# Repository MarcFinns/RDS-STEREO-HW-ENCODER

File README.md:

# RDS Stereo Encoder for FM radio 

A hardware RDS Stereo Encoder for FM radio comprised of:
- A signal processing board
- A digital board that provides a transparent communication bridge between PC RDS software and the DS encoder chips, while simultaneously providing real-time visual display of RDS data (PS/RT) and audio levels (VU meters) on a TFT display.

## System Overview

This project specifically describes the software implementation of the digital board. The schematic and PCB of the whole system are in the **HARDWARE** folder.

### Key Features

- **Dual-core ESP32 processing** for optimal performance
- **FreeRTOS task-based design** with priority optimization
- **Queue-based inter-task communication** for thread safety
- **Collision avoidance system** for seamless PC-MRDS1322 bridging
- **Real-time graphics** with ~60 FPS VU meter updates
- **Professional VU meters** with color-coded zones and peak detection

## Hardware Requirements

### Main Components
- **ESP32 DevKit** (dual-core processing)
- **MRDS1322 RDS encoder chip**
- **NV3007 428x142 TFT display**
- **Dual-channel audio input** for VU meters

### Hardware Design Files

The **`hardware/`** folder contains the complete PCB design for this project, including schematics and PCB layout. This hardware has been **built and fully tested** in real-world conditions.

### MRDS1322 RDS Encoder

The **MRDS1322** RDS encoder chip is from [Pira.cz](http://pira.cz). Datasheet available in the `hardware/` folder. Use the **TinyRDS** Windows program (also from Pira.cz) to send RDS data through this ESP32 bridge to the encoder.

## Pin Assignments

### TFT Display (NV3007) - SPI Interface
```
ESP32 Pin | Function    | NV3007 Pin
----------|-------------|-------------
GPIO19    | SCLK        | SCK
GPIO18    | MOSI        | SDA
GPIO16    | CS          | CS
GPIO17    | DC/RS       | DC
GPIO5     | RST         | RES
GPIO4     | Backlight   | LED
3.3V      | Power       | VCC
GND       | Ground      | GND
```

### Serial Communication
```
Interface | ESP32 Pin    | Baud Rate | Purpose
----------|------------- |-----------|------------------
Serial    | USB          | 19200     | PC Communication
Serial1   | GPIO21 (RX)  | 19200     | MRDS1322 RDS Chip
          | GPIO22 (TX)  |           |
```

### VU Meters - Audio Input (ADC)
```
Channel | ESP32 Pin | ADC Channel | Purpose
--------|-----------|-------------|----------------
Left    | GPIO39    | ADC1_CH3    | Left audio input
Right   | GPIO36    | ADC1_CH0    | Right audio input
```

### Complete Pin Reference Table
All pin assignments are centralized in `SharedTypes.h` for easy modification:

```
┌──────────────┬─────────────────────┬──────────────────────────┐
│ ESP32 GPIO   │ Function            │ Connected To             │
├──────────────┼─────────────────────┼──────────────────────────┤
│ GPIO21       │ SERIAL1_RX          │ MRDS1322 TX              │
│ GPIO22       │ SERIAL1_TX          │ MRDS1322 RX              │
│ GPIO16       │ TFT_CS              │ NV3007 Chip Select       │
│ GPIO5        │ TFT_RST             │ NV3007 Reset             │
│ GPIO17       │ TFT_DC              │ NV3007 Data/Command      │
│ GPIO18       │ TFT_MOSI            │ NV3007 SPI Data          │
│ GPIO19       │ TFT_SCLK            │ NV3007 SPI Clock         │
│ GPIO4        │ TFT_BL              │ NV3007 Backlight         │
│ GPIO39 (A3)  │ PIN_L (ADC1_CH3)    │ Left Audio Input         │
│ GPIO36 (A0)  │ PIN_R (ADC1_CH0)    │ Right Audio Input        │
│ USB (N/A)    │ Serial (PC Comm)    │ PC USB Connection        │
└──────────────┴─────────────────────┴──────────────────────────┘
```

**Note**: All pin defines are located in `SharedTypes.h` lines 136-151. To change pin assignments for PCB design, simply modify the `#define` values in that single location.

## System Architecture

### Communication Flow
```
PC Software → Serial USB → ESP32 Core 0 → Serial1 → MRDS1322
                ↓              ↓
         Response Routing  PS/RT Monitoring
                ↓              ↓
            PC Software    Core 1 → TFT Display
                               ↓
                          VU Meters (GPIO36/39)
```

### Task Architecture
- **CommunicationManager** (Core 0, Priority 1): PC-MRDS1322 bridging
- **DisplayManager** (Core 1, Priority 2): TFT graphics + VU meters
- **Queue-based data exchange** for thread-safe operation

## Display Layout

### TFT Display (428x142, Landscape)
```
┌─────────────────────────────────┐ ← Y=10
│         STATION ID              │   Station area (30px tall)
│      (Cyan, Size 3)             │   Auto-centered, space-trimmed
├─────────────────────────────────┤ ← Y=38
│   Scrolling Radio Text...       │   Text area (25px tall)
│     (White, Size 2)             │   Sliding window scrolling
├─────────────────────────────────┤ ← Y=75
│ L ████████████████████████████  │   VU Left (18px tall)
│   |   |  |  ||  |     dB Scale  │   Professional scale with
│  -20 -10 -3  0 +3   (colored)   │   color-coded bold labels
│   |   |  |  ||  |               │
│ R ████████████████████████████  │   VU Right (18px tall)
└─────────────────────────────────┘ ← Y=142
```

### VU Meter Features
- **Color-coded bars**: Green (safe) → Yellow (loud) → Orange (hot) → Red (peak)
- **Professional dB scale**: Centered between bars with color-coded bold labels
  - **-20/-10 dB**: Green (safe levels)
  - **-3 dB**: Yellow (caution level)
  - **0 dB**: White (reference level)
  - **+3 dB**: Red (peak/overload warning)
- **Peak markers**: White bars showing recent maximum levels (1-second hold)
- **Smooth ballistics**: Fast attack, slow release for natural VU behavior

## MRDS1322 Protocol

### Memory Map
- **PS (Program Service)**: Address 0xC8, Length 8 bytes
- **RT (Radio Text)**: Address 0x20, Length 64 bytes

### Protocol Frame Structure
```
Read Command:  FE D0 [ADDR] [LEN] FF
Response:      FE [DATA...] FF

Byte Stuffing Rules:
- Data byte 0xFD → FD 00
- Data byte 0xFE → FD 01
- Data byte 0xFF → FD 02
```

## Configuration

### VU Meter Parameters
```cpp
#define SAMPLE_WINDOW 2       // Samples per level calculation
#define ATTACK_STEP 3         // Fast attack (pixels/step)
#define RELEASE_STEP 4        // Slow release (pixels/step)
#define DECAY_INTERVAL_MS 20  // Decay timing (20ms)
#define PEAK_HOLD_MS 1000     // Peak hold time (1 second)
```

### Text Scrolling
```cpp
#define SCROLL_DELAY_MS 50    // Base scroll timing (multiplied by 3 = 150ms actual)
#define SCROLL_STEP_SIZE 2    // Pixels to advance per step (smooth motion)
```

### Display Features
- **Station ID**: Auto-centers after trimming trailing spaces
- **Radio Text**: Sliding window scrolling for long text, centered for short text
- **VU Scale**: Professional dB scale with bold, color-coded labels

## Performance Specifications

- **VU Meter Update Rate**: ~60 FPS (16ms loop time)
- **Text Scroll Speed**: Character-by-character at ~6.7 FPS (150ms per step)
- **MRDS1322 Polling**: Every 2 seconds
- **Peak Marker Hold**: 1 second
- **Audio Sampling**: 12-bit ADC (0-4095 range)
- **Display Updates**: Change detection prevents unnecessary redraws

## Build Dependencies

### Required Libraries
```cpp
#include <Arduino.h>
#include <Arduino_GFX_Library.h>    // TFT display driver (NV3007)
#include "freertos/FreeRTOS.h"      // Real-time OS
#include "freertos/queue.h"         // Inter-task communication
#include "freertos/task.h"          // Task management
```

## File Structure

```
RDS_STEREO_ENCODER_CLEAN/
├── RDS_STEREO_ENCODER_CLEAN.ino  # Main Arduino sketch
├── CommunicationManager.h        # PC-MRDS1322 bridge header
├── CommunicationManager.cpp      # Communication implementation
├── DisplayManager.h              # Display management header
├── DisplayManager.cpp            # TFT/VU meter implementation
├── SharedTypes.h                 # Pin configuration & data structures
├── splashscreen.h                # Splash screen data header
├── splashscreen.cpp              # Splash screen bitmap data
└── README.md                     # This documentation
```

## Usage

1. **Hardware Setup**: Connect all components according to pin assignments
2. **Software Setup**: Install required libraries in Arduino IDE
3. **Configuration**: Adjust compile-time options in SharedTypes.h
4. **Upload**: Flash the code to ESP32 DevKit
5. **PC Software**: Connect RDS software to ESP32's Serial port at 19200 baud
6. **MRDS1322**: Connect RDS encoder chip to Serial1 at 19200 baud

## License

Created by Claude Code Assistant, 2024
Version 2.0

## Technical Notes

- The system uses ESP32's dual-core architecture for optimal performance
- Core 0 handles communication with lower priority for smooth graphics
- Core 1 handles display updates with higher priority for responsive VU meters
- Queue-based communication ensures thread-safe data exchange
- Change detection prevents unnecessary screen updates and reduces flicker
- Logarithmic audio scaling provides perceptual accuracy for VU meters

## Pin Configuration for PCB Design

All hardware pin assignments are centralized in **`SharedTypes.h`** (lines 136-151) under the section "ESP32 HARDWARE PIN CONFIGURATION". This design makes it easy to modify pins for custom PCB layouts:

1. **Serial Communication**: `SERIAL1_RX`, `SERIAL1_TX` (GPIO21/22)
2. **TFT Display**: `TFT_CS`, `TFT_RST`, `TFT_DC`, `TFT_MOSI`, `TFT_SCLK`, `TFT_BL` (GPIO16/5/17/18/19/4)
3. **VU Meter ADC**: `PIN_L`, `PIN_R` (GPIO39/36)

**To modify pins**: Simply edit the `#define` values in `SharedTypes.h`. The code automatically uses these definitions throughout - no need to search and replace in multiple files.

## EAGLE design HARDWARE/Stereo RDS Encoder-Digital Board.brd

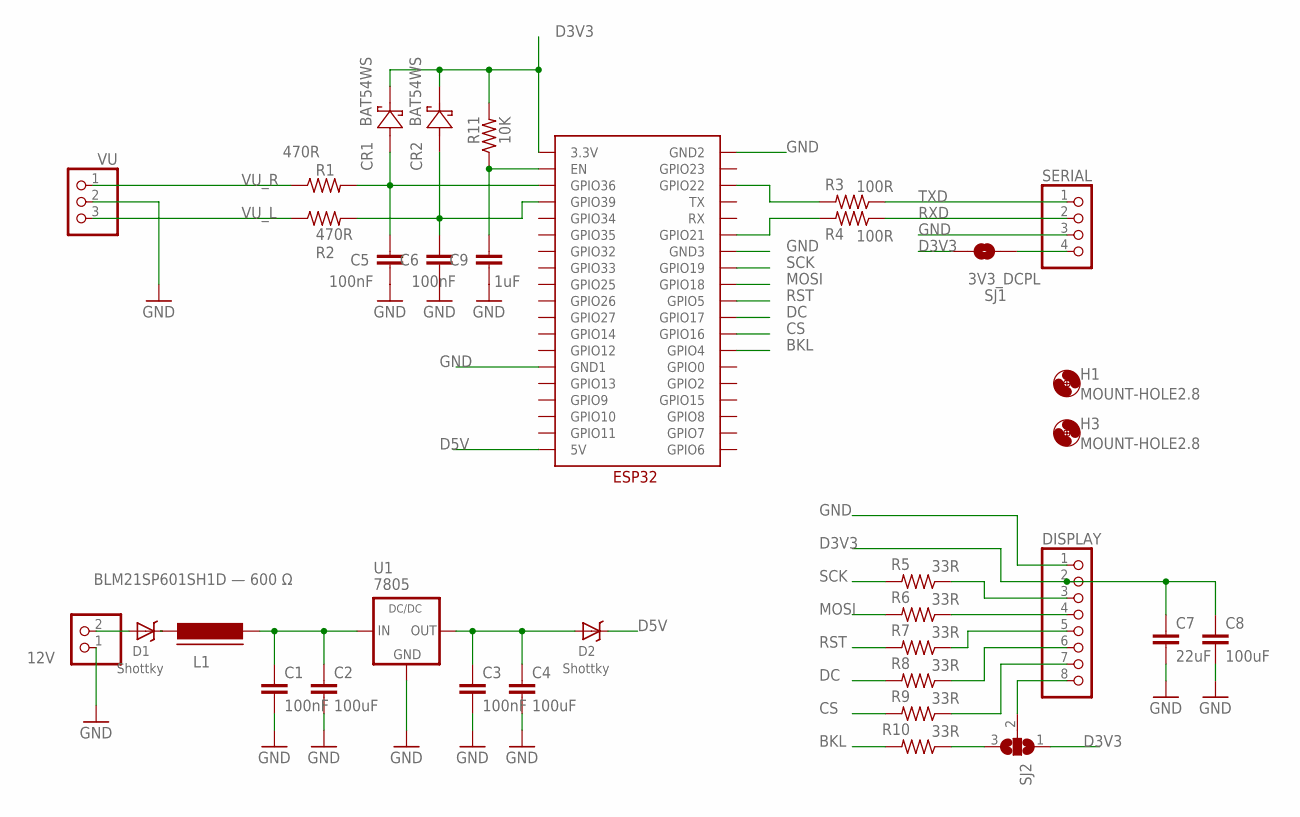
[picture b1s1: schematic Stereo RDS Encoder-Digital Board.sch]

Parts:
12V: PINHD-1X2; 1X02
C1, C3, C5, C6: 100nF; C0805
C2, C4, C8: 100uF; C0805
C7: 22uF; C0805
C9: 1uF; C0805
CR1, CR2: BAT54WS; SDO_SOD-323_VIS
D1, D2: Shottky; SMA-403D
DEV1: ESP32
DISPLAY: PINHD-1X8; 1X08
H1, H3: MOUNT-HOLE2.8; 2,8
L1: BLM21SP601SH1D — 600 Ω; FB805
R1, R2: 470R; M0805
R3, R4: 100R; M0805
R5, R6, R7, R8, R9, R10: 33R; M0805
R11: 10K; M0805
SERIAL: PINHD-1X4; 1X04
SJ1: 3V3_DCPL; SJ_2S-NO
SJ2: SJ2W; SJ_2
U1: 7805; R-78XX
VU: PINHD-1X3; 1X03

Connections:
BKL: DEV1.GPIO4, R10.2
CS: DEV1.GPIO16, R9.2
D3V3: C7.1, C8.1, CR1.1 (CATHODE), CR2.1 (CATHODE), DEV1.3.3V, DISPLAY.2, R11.2, SJ1.1, SJ2.1
D5V: D2.C, DEV1.5V
D5V1: C1.1, C2.1, L1.2, U1.1 (IN)
DC: DEV1.GPIO17, R8.2
GND: 12V.1, C1.2, C2.2, C3.2, C4.2, C5.2, C6.2, C7.2, C8.2, C9.2, DEV1.GND1, DEV1.GND2, DEV1.GND3, DISPLAY.1, SERIAL.3, U1.2 (GND), VU.2
MOSI: DEV1.GPIO18, R6.2
unnamed: R10.1, SJ2.3
unnamed: DEV1.GPIO21, R4.2
unnamed: DEV1.GPIO22, R3.2
unnamed: SERIAL.4, SJ1.2
unnamed: C9.1, DEV1.EN, R11.1
unnamed: D1.C, L1.1
unnamed: 12V.2, D1.A
unnamed: C5.1, CR1.2 (ANODE), DEV1.GPIO36, R1.2
unnamed: C6.1, CR2.2 (ANODE), DEV1.GPIO39, R2.2
unnamed: DISPLAY.3, R5.1
unnamed: DISPLAY.4, R6.1
unnamed: DISPLAY.5, R7.1
unnamed: DISPLAY.6, R8.1
unnamed: DISPLAY.7, R9.1
unnamed: DISPLAY.8, SJ2.2
unnamed: C3.1, C4.1, D2.A, U1.3 (OUT)
RST: DEV1.GPIO5, R7.2
RXD: R4.1, SERIAL.2
SCK: DEV1.GPIO19, R5.2
TXD: R3.1, SERIAL.1
VU_L: R2.1, VU.3
VU_R: R1.1, VU.1

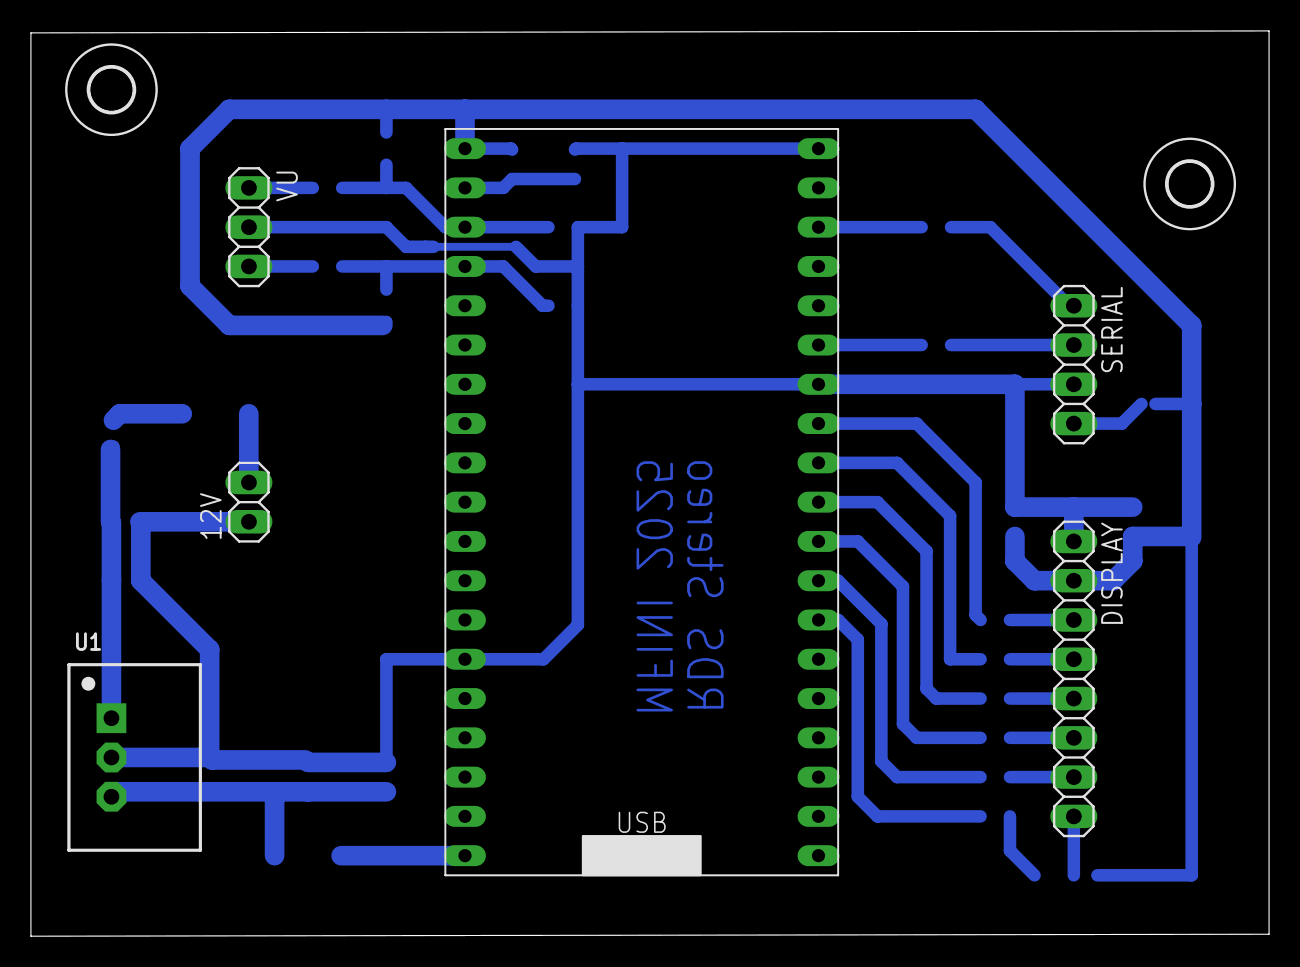
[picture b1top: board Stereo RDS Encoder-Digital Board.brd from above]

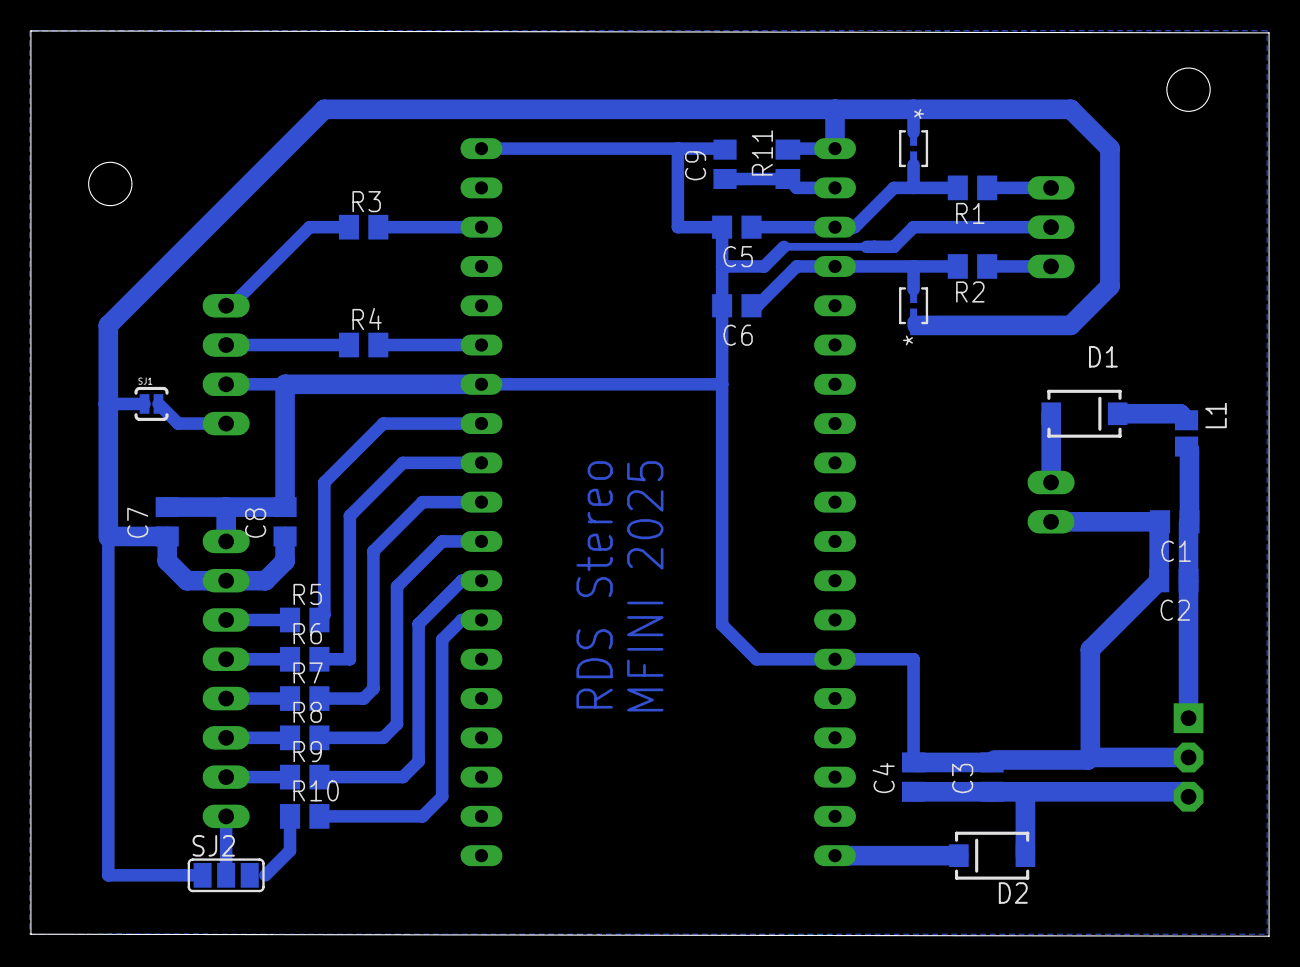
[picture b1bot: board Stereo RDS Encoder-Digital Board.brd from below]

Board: 2 copper layers, 80.1 x 58.5 mm, 35 parts (27 on the bottom side), 30 nets.

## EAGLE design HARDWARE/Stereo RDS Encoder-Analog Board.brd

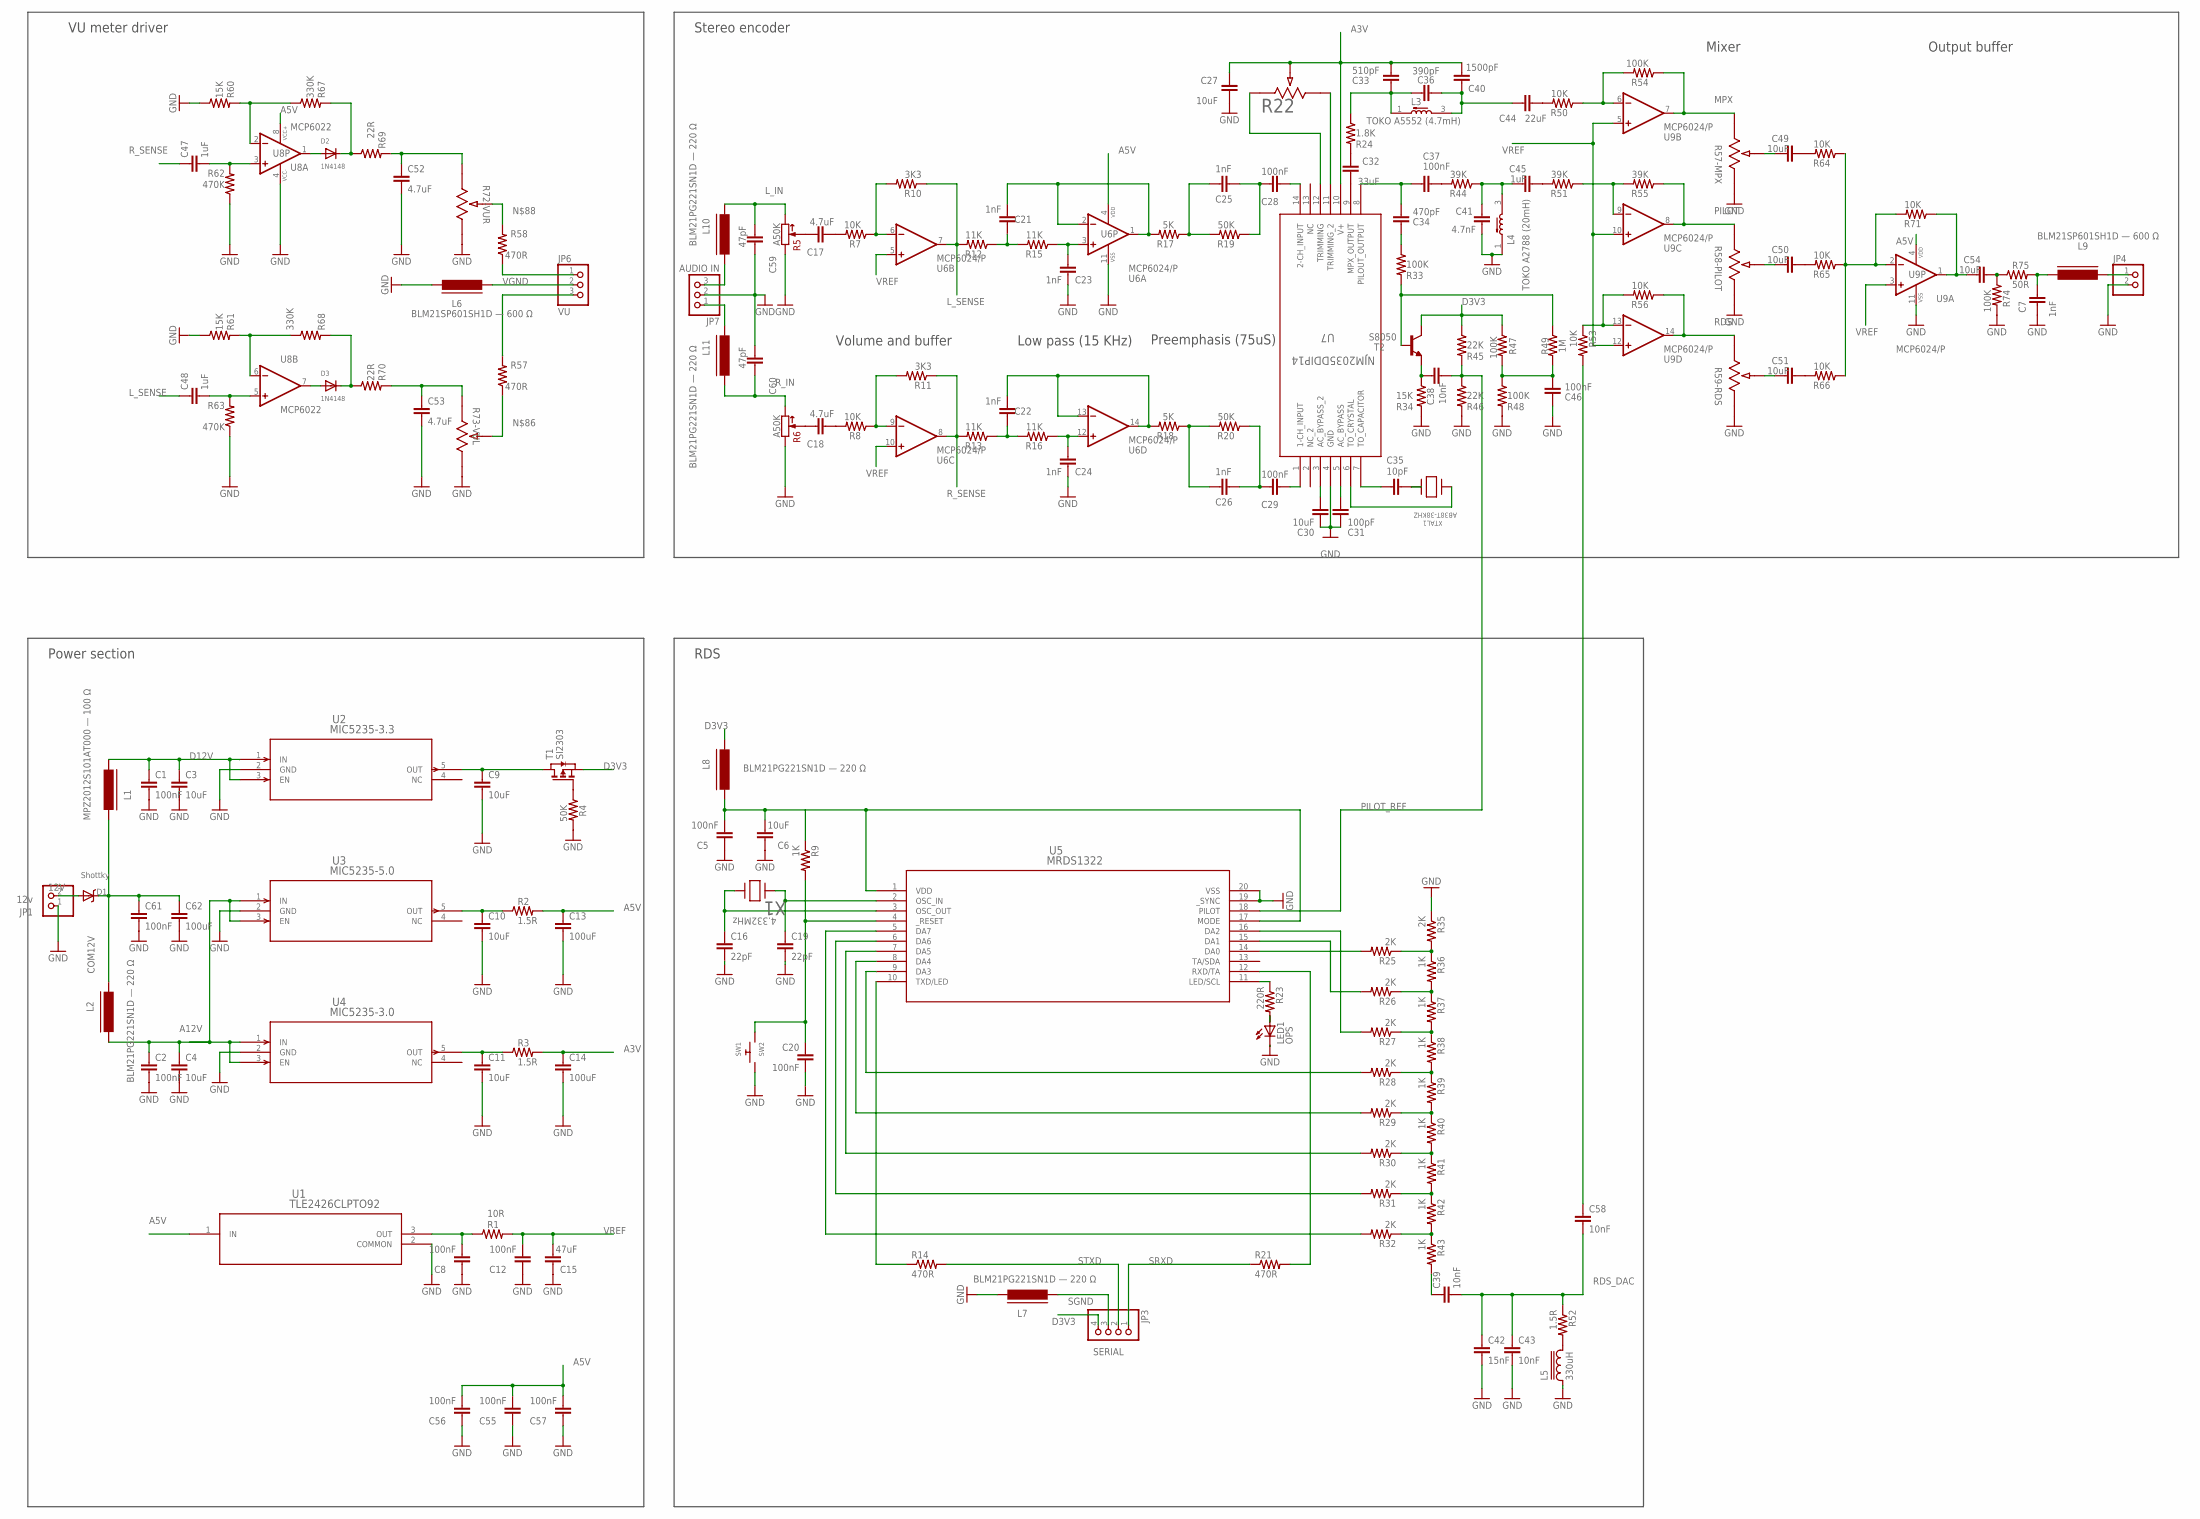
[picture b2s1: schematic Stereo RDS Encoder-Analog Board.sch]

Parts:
C1, C2, C5, C8, C12, C20, C28, C29, C37, C46, C55, C56, C57, C61: 100nF; C0805
C3, C4, C6, C9, C10, C11, C27, C30, C49, C50, C51, C54: 10uF; C0805
C7, C21, C22, C23, C24, C25, C26: 1nF; C0805
C13, C14, C62: 100uF; C0805
C15: 47uF; C0805
C16, C19: 22pF; C0805
C17, C18, C52, C53: 4.7uF; C0805
C31: 100pF; C0805
C32: 33uF; C0805
C33: 510pF; C0805
C34: 470pF; C0805
C35: 10pF; C0805
C36: 390pF; C0805
C38, C39, C43, C58: 10nF; C0805
C40: 1500pF; C0805
C41: 4.7nF; C0805
C42: 15nF; C0805
C44: 22uF; C0805
C45, C47, C48: 1uF; C0805
C59, C60: 47pF; C0805
D1: Shottky; SMA-403D
D2, D3: 1N4148; SOD-323F
JP1: 12v; 1X02
JP3: SERIAL; 1X04
JP4: PINHD-1X2; 1X02
JP6: VU; 1X03
JP7: AUDIO IN; 1X03
L1: MPZ2012S101AT000 — 100 Ω; FB805
L2, L7, L8, L10, L11: BLM21PG221SN1D — 220 Ω; FB805
L3: TOKO A5552 (4.7mH); 7KMM
L4: TOKO A2788 (20mH); 7KMM
L5: 330uH; 8RB
L6, L9: BLM21SP601SH1D — 600 Ω; FB805
LED1: OPS; CHIPLED_0805
R1: 10R; M0805
R2, R3, R52: 1.5R; M0805
R4, R19, R20: 50K; M0805
R5, R6: A50K; RV09-SINGLE
R7, R8, R50, R53, R56, R64, R65, R66, R71: 10K; M0805
R9, R36, R37, R38, R39, R40, R41, R42, R43: 1K; M0805
R10, R11: 3K3; M0805
R12, R13, R15, R16: 11K; M0805
R14, R21, R57, R58: 470R; M0805
R17, R18: 5K; M0805
R22, R57-MPX, R58-PILOT, R59-RDS, R72-VUR, R73-VUL: 50K; POT_3296W
R23: 220R; M0805
R24: 1.8K; M0805
R25, R26, R27, R28, R29, R30, R31, R32, R35: 2K; M0805
R33, R47, R48, R54, R74: 100K; M0805
R34, R60, R61: 15K; M0805
R44, R51, R55: 39K; M0805
R45, R46: 22K; M0805
R49: 1M; M0805
R62, R63: 470K; M0805
R67, R68: 330K; M0805
R69, R70: 22R; M0805
R75: 50R; M0805
SW1: SW2; BTN_CK_KSS
T1: SI2303; SOT-23
T2: S8050; SOT23
U1: TLE2426CLPTO92; TO92
U2: MIC5235-3.3; SOT-23-5_M5_MCH-M
U3: MIC5235-5.0; SOT-23-5_M5_MCH-M
U4: MIC5235-3.0; SOT-23-5_M5_MCH-M
U5: MRDS1322; PDIP20_300MC_MCH
U6, U9: MCP6024/P; DIL14
U7: NJM2035DDIP14; DIP14
U8: MCP6022; DIL08
X1: 4.332MHz; XTAL_HC-49/U-S_CFC
XTAL1: AB38T-38KHZ; XTAL_AB38T_ABR

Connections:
12V: D1.A, JP1.2
A3V: C14.1, C27.1, C33.1, C40.1, R3.2, R22.2, U7.10 (V+)
A5V: C13.1, C55.2, C56.2, C57.2, R2.2, U1.1 (IN), U6.4 (VDD), U8.8 (VCC+), U9.4 (VDD)
A12V: C2.1, C4.1, L2.2, U3.1 (IN), U3.3 (EN), U4.1 (IN), U4.3 (EN)
COM12V: C61.1, C62.1, D1.C, L1.1, L2.1
D3V3: JP3.4, L8.1, R45.1, R47.1, T1.2 (S), T2.3 (C)
D12V: C1.1, C3.1, L1.2, U2.1 (IN), U2.3 (EN)
GND: C1.2, C2.2, C3.2, C4.2, C5.1, C6.1, C7.1, C8.1, C9.2, C10.2, C11.2, C12.1, C13.2, C14.2, C15.1, C16.2, C19.2, C20.2, C23.1, C24.1, C27.2, C30.1, C31.1, C41.1, C42.2, C43.2, C46.1, C52.2, C53.2, C55.1, C56.1, C57.1, C59.1, C60.2, C61.2, C62.2, JP1.1, JP4.2, JP7.2, L4.1 (L1), L5.1, L6.1, L7.1, LED1.C, R4.2, R5.1 (CCW), R6.1 (CCW), R34.2, R35.1, R46.2, R48.2, R57-MPX.3, R58-PILOT.3, R59-RDS.3, R60.1, R61.1, R62.1, R63.1, R72-VUR.3, R73-VUL.3, R74.2, SW1.P$2, U1.2 (COMMON), U2.2 (GND), U3.2 (GND), U4.2 (GND), U5.19 (_SYNC), U5.20 (VSS), U6.11 (VSS), U7.4 (GND), U8.4 (VCC-), U9.11 (VSS)
L_IN: C59.2, L10.1, R5.3 (CW)
L_SENSE: C48.1, R10.1, R12.2, U6.7 (OUT)
MPX: R54.1, R57-MPX.1, U9.7 (OUT)
N#222: C9.1, T1.1 (D), U2.5 (OUT)
unnamed: C16.1, U5.3 (OSC_OUT), X1.2
unnamed: C19.1, U5.2 (OSC_IN), X1.1
unnamed: R23.1, U5.11 (LED/SCL)
unnamed: R25.1, R35.2, R36.1
unnamed: R26.1, R36.2, R37.1
unnamed: R27.1, R37.2, R38.1
unnamed: R28.1, R38.2, R39.1
unnamed: R29.1, R39.2, R40.1
unnamed: R30.1, R40.2, R41.1
unnamed: R31.1, R41.2, R42.1
unnamed: R32.1, R42.2, R43.1
unnamed: R25.2, U5.14 (DA0)
unnamed: R26.2, U5.15 (DA1)
unnamed: R27.2, U5.16 (DA2)
unnamed: R28.2, U5.9 (DA3)
unnamed: R29.2, U5.8 (DA4)
unnamed: R30.2, U5.7 (DA5)
unnamed: R31.2, U5.6 (DA6)
unnamed: R32.2, U5.5 (DA7)
unnamed: C39.1, R43.2
unnamed: R22.3, U7.11 (TRIMMING_2)
unnamed: R60.2, R67.1, U8.2 (-IN)
unnamed: LED1.A, R23.2
unnamed: D2.A, U8.1 (OUT)
unnamed: D2.C, R67.2, R69.1
unnamed: C47.2, R62.2, U8.3 (+IN)
unnamed: C17.1, R5.2 (W)
unnamed: R61.2, R68.1, U8.6 (-IN)
unnamed: C17.2, R7.2
unnamed: R7.1, R10.2, U6.6 (-IN)
unnamed: C8.2, R1.1, U1.3 (OUT)
unnamed: C21.1, R12.1, R15.2
unnamed: C23.2, R15.1, U6.3 (+IN)
unnamed: C21.2, R17.2, U6.1 (OUT), U6.2 (-IN)
unnamed: C25.2, R17.1, R19.2
unnamed: C25.1, C28.1, R19.1
unnamed: C28.2, U7.14 (2-CH_INPUT)
unnamed: C18.1, R6.2 (W)
unnamed: C18.2, R8.2
unnamed: R8.1, R11.2, U6.9 (-IN)
unnamed: C11.1, R3.1, U4.5 (OUT)
unnamed: C22.1, R13.1, R16.2
unnamed: C24.2, R16.1, U6.12 (+IN)
unnamed: C22.2, R18.2, U6.13 (-IN), U6.14 (OUT)
unnamed: C26.2, R18.1, R20.2
unnamed: C26.1, C29.1, R20.1
unnamed: C29.2, U7.1 (1-CH_INPUT)
unnamed: C30.2, U7.3 (AC_BYPASS_2)
unnamed: C31.2, U7.5 (AC_BYPASS)
unnamed: C35.2, U7.7 (TO_CAPACITOR)
unnamed: C35.1, XTAL1.2
unnamed: U7.6 (TO_CRYSTAL), XTAL1.1
unnamed: R22.1, U7.12 (TRIMMING)
unnamed: D3.A, U8.7 (OUT)
unnamed: C41.2, C45.1, L4.3 (L2), R44.1
unnamed: C34.1, C37.2, U7.8 (PILOUT_OUTPUT)
unnamed: C37.1, R44.2
unnamed: C32.2, U7.9 (MPX_OUTPUT)
unnamed: C32.1, R24.2
unnamed: C33.2, C36.1, L3.1 (L1), R24.1
unnamed: R51.1, R55.2, U9.9 (-IN)
unnamed: R50.1, R54.2, U9.6 (-IN)
unnamed: R53.1, R56.2, U9.13 (-IN)
unnamed: C44.2, R50.2
unnamed: C45.2, R51.2
unnamed: C49.1, R57-MPX.2
unnamed: C50.1, R58-PILOT.2
unnamed: C51.1, R59-RDS.2
unnamed: C49.2, R64.2
unnamed: C50.2, R65.2
unnamed: C51.2, R66.2
unnamed: R64.1, R65.1, R66.1, R71.2, U9.2 (-IN)
unnamed: D3.C, R68.2, R70.1
unnamed: C34.2, R33.1
unnamed: C58.1, R53.2
unnamed: C52.1, R69.2, R72-VUR.1
unnamed: C53.1, R70.2, R73-VUL.1
unnamed: L5.2, R52.2
unnamed: C54.1, R71.1, U9.1 (OUT)
unnamed: JP7.3, L10.2
unnamed: JP7.1, L11.1
unnamed: C10.1, R2.1, U3.5 (OUT)
unnamed: R33.2, R49.1, T2.1 (B)
unnamed: C46.2, R47.2, R48.1, R49.2
unnamed: R4.1, T1.3 (G)
unnamed: R57.1, R73-VUL.2
unnamed: C38.1, R34.1, T2.2 (E)
unnamed: R58.2, R72-VUR.2
unnamed: C54.2, R74.1, R75.1
unnamed: C7.2, L9.2, R75.2
unnamed: JP4.1, L9.1
unnamed: C36.2, C40.2, C44.1, L3.3 (L2)
unnamed: C48.2, R63.2, U8.5 (+IN)
PIC3V3: C5.2, C6.2, L8.2, R9.1, U5.1 (VDD), U5.17 (MODE)
PILOT: R55.1, R58-PILOT.1, U9.8 (OUT)
PILOT_REF: C38.2, R45.2, R46.1, U5.18 (PILOT)
RDS: R56.1, R59-RDS.1, U9.14 (OUT)
RDS_DAC: C39.2, C42.1, C43.1, C58.2, R52.1
RST: C20.1, R9.2, SW1.P$1, U5.4 (_RESET)
RXD: R21.2, U5.12 (RXD/TA)
R_IN: C60.1, L11.2, R6.3 (CW)
R_SENSE: C47.1, R11.1, R13.2, U6.8 (OUT)
SGND: JP3.3, L7.2
SRXD: JP3.1, R21.1
STXD: JP3.2, R14.2
TXD: R14.1, U5.10 (TXD/LED)
VGND: JP6.2, L6.2
VREF: C12.2, C15.2, R1.2, U6.5 (+IN), U6.10 (+IN), U9.3 (+IN), U9.5 (+IN), U9.10 (+IN), U9.12 (+IN)
VU_L: JP6.3, R57.2
VU_R: JP6.1, R58.1

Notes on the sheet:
Power section
Stereo encoder
RDS
VU meter driver
Volume and buffer
Low pass (15 KHz)
Preemphasis (75uS)
Mixer
Output buffer

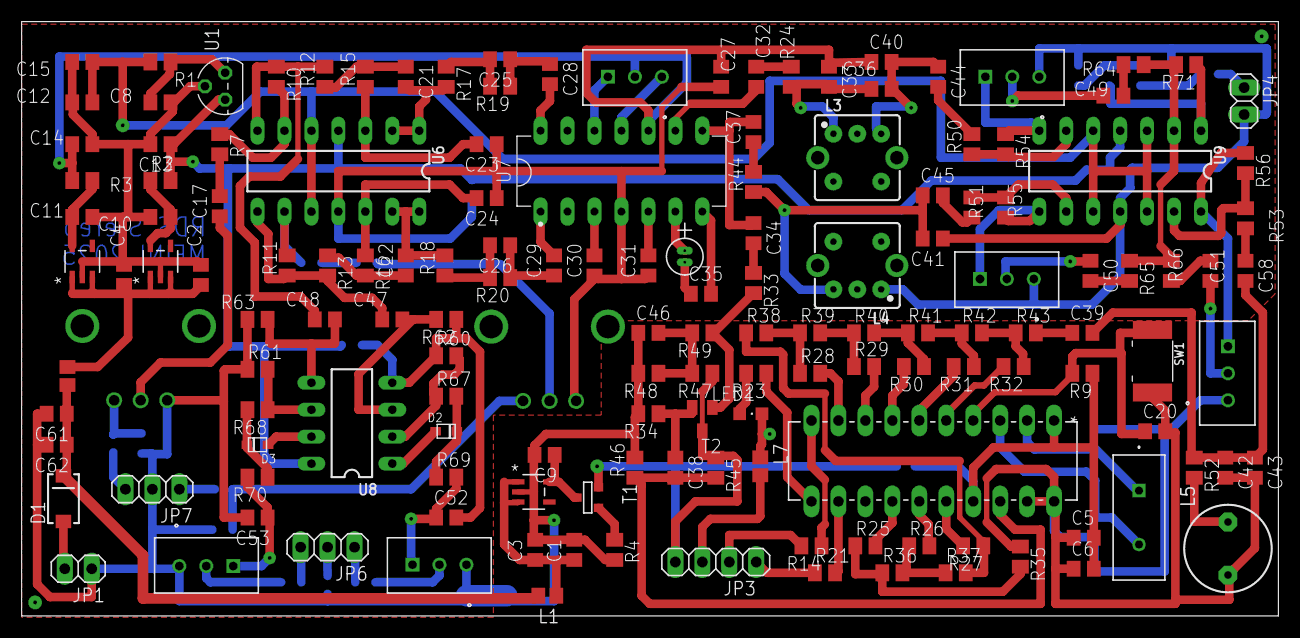
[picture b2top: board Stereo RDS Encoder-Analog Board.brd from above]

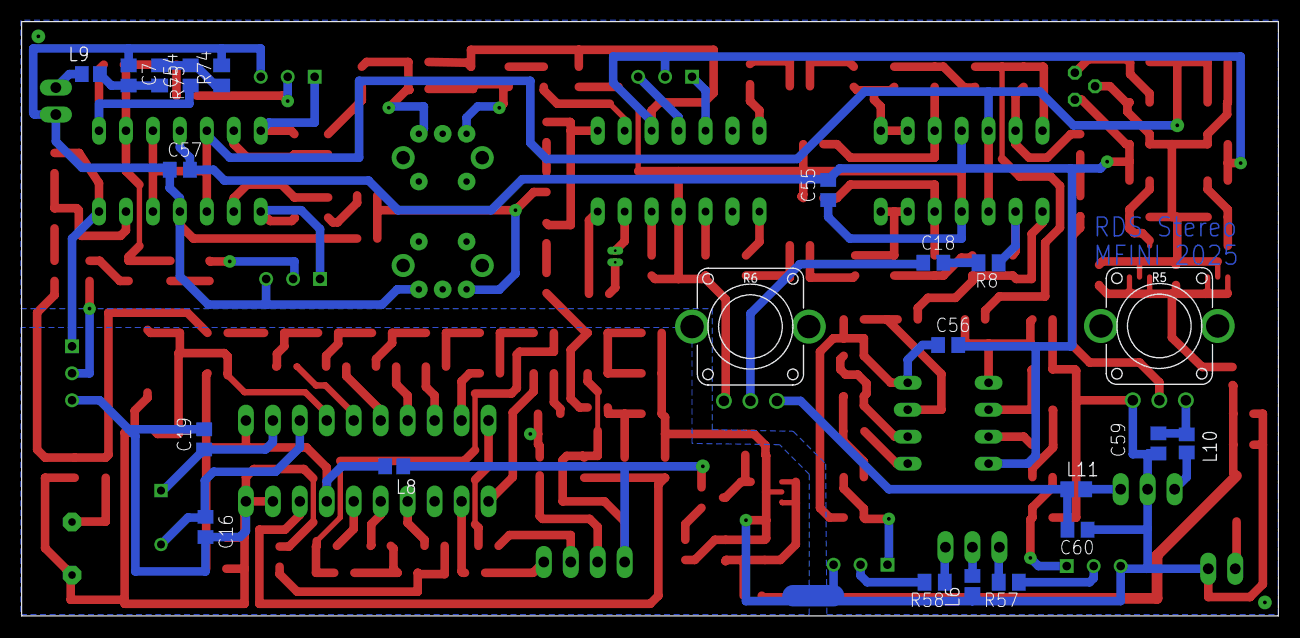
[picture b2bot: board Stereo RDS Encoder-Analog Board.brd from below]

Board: 2 copper layers, 118.4 x 56.0 mm, 173 parts (22 on the bottom side), 122 nets.

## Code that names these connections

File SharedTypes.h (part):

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 *
 * File:         SharedTypes.h
 * Description:  Central configuration and shared data structures for the ESP32
 * RDS encoder bridge system. Contains all constants, data types, and hardware
 * definitions used across the entire project.
 *
 * System Architecture:
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 *
 * Hardware Setup:
 *   - ESP32 DevKit with dual-core processing
 *   - MRDS1322 RDS encoder chip (Serial1, GPIO21/22, 19200 baud)
 *   - NV3007 428x142 TFT display (SPI, GPIO16/17/18/19, landscape mode)
 *   - Dual-channel audio input for VU meters (GPIO36/39, ADC pins A0/A3)
 *
 * Communication Flow:
 *   PC → ESP32 (Serial USB) → MRDS1322 (Serial1) → ESP32 → TFT Display
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 */

// ===== SERIAL COMMUNICATION PINS =====
#define SERIAL1_RX 21 // MRDS1322 RX pin (GPIO21)
#define SERIAL1_TX 22 // MRDS1322 TX pin (GPIO22)
// Note: Serial (USB) uses default pins and is initialized separately

// ===== TFT DISPLAY PINS (NV3007 - SPI Interface) =====
#define TFT_CS 16   // Chip Select (GPIO16)
#define TFT_RST 5   // Reset (GPIO5)
#define TFT_DC 17   // Data/Command (GPIO17)
#define TFT_MOSI 18 // SPI MOSI Data (GPIO18)
#define TFT_SCLK 19 // SPI Clock (GPIO19)
#define TFT_BL 4    // Backlight Control (GPIO4)

// ===== VU METER ADC INPUT PINS =====
#define PIN_L A3 // Left audio channel: GPIO39 (ADC1_CH3)
#define PIN_R A0 // Right audio channel: GPIO36 (ADC1_CH0)

/*
 * Complete Pin Assignment Reference:
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 * ┌──────────────┬─────────────────────┬──────────────────────────┐
 * │ ESP32 GPIO   │ Function            │ Connected To             │
 * ├──────────────┼─────────────────────┼──────────────────────────┤
 * │ GPIO21       │ SERIAL1_RX          │ MRDS1322 TX              │
 * │ GPIO22       │ SERIAL1_TX          │ MRDS1322 RX              │
 * │ GPIO16       │ TFT_CS              │ NV3007 Chip Select       │
 * │ GPIO5        │ TFT_RST             │ NV3007 Reset             │
 * │ GPIO17       │ TFT_DC              │ NV3007 Data/Command      │
 * │ GPIO18       │ TFT_MOSI            │ NV3007 SPI Data          │
 * │ GPIO19       │ TFT_SCLK            │ NV3007 SPI Clock         │
 * │ GPIO4        │ TFT_BL              │ NV3007 Backlight         │
 * │ GPIO39 (A3)  │ PIN_L (ADC1_CH3)    │ Left Audio Input         │
 * │ GPIO36 (A0)  │ PIN_R (ADC1_CH0)    │ Right Audio Input        │
 * │ USB (N/A)    │ Serial (PC Comm)    │ PC USB Connection        │
 * └──────────────┴─────────────────────┴──────────────────────────┘
 */
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
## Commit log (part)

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2025-10-20 Revise README for clarity and detail
    Updated project description and clarified system overview.

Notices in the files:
parts and their libraries:
op-amp: Copyright (C) 2015, Bob Starr
inductor-toko: Copyright (C) 2010, Bob Starr
COPYRIGHT: Copyright (C) 2025 Ultra Librarian. All rights reserved.
SparkFun-Aesthetics: Licensing: Creative Commons ShareAlike 4.0 International - https://creativecommons.org/licenses/by-sa/4.0
